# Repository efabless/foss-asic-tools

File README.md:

# IIC-OSIC-TOOLS

This environment is based on the [efabless.com FOSS-ASIC-TOOLS](https://github.com/efabless/foss-asic-tools).

**IIC-OSIC-TOOLS** is an all-in-one Docker container for open-source-based integrated circuit designs for analog and digital circuit flows. The CPU architectures `x86_64/amd64` and `aarch64/arm64` are natively supported based on Ubuntu 22.04LTS (since release `2022.12`). This collection of tools is curated by the [**Institute for Integrated Circuits (IIC), Johannes Kepler University (JKU)**](https://iic.jku.at).

It supports two *modes of operation*:

1. Using a complete desktop environment (XFCE) in `Xvnc` (a VNC server), either directly accessing it with a VNC client of your choice or the integrated [noVNC](https://novnc.com) server that runs in your browser.
2. Using a local X11 server and directly showing the application windows on your desktop.

## How to Use These Open-Source (and Free) IC Design Tools

### Step 1: Clone/download this GitHub repository onto your computer

Use the green **Code** button, and either download the zip file or do a `git clone --depth=1 https://github.com/iic-jku/iic-osic-tools.git`.

### Step 2: Install Docker on your computer

See instructions on how to do this in the section [**Quick Launch for Designers**](#quick-launch-for-designers) further down in this `README`.

### Step 3: Start and Use a Docker Container based on our IIC-OSIC-TOOLS Image

Enter the directory of this repository on your computer, and use one of the methods described in the section [**Quick Launch for Designers**](#quick-launch-for-designers) to start up and run a Docker container based on our image. The easiest way is probably to use the **VNC** mode.

If you do this the first time, or we have pushed an updated image to DockerHub, this can take a while since the image is pulled (loaded) automatically from DockerHub. Since this image is ca. 4GB, this takes time, depending on your internet speed. Please note that this compressed image will be extracted on your drive, so please provide at least **20GB of free drive space**. If, after a while, the consumed space gets larger, this may be due to unused images piling up. In this case, delete old ones; please consult the internet for instructions on operating Docker.

If you know what you are doing and want full root access without a graphical interface, please use `./start_shell.sh`.

## Installed PDKs

As of the `2022.12` tag, the following open-source process-development kits (PDKs) are pre-installed, and the table shows how to switch by setting environment variables (you can do this per project by putting this into `.designinit` as explained below):

| SkyWater Technologies `sky130A` |
|---|
| `export PDK=sky130A` |
| `export PDKPATH=$PDK_ROOT/$PDK` |
| `export STD_CELL_LIBRARY=sky130_fd_sc_hd` |

| Global Foundries `gf180mcuC` |
|---|
| `export PDK=gf180mcuC` |
| `export PDKPATH=$PDK_ROOT/$PDK` |
| `export STD_CELL_LIBRARY=gf180mcu_fd_sc_mcu7t5v0` |

| IHP Microelectronics `sg13g2` |
|---|
| Not yet ready to use |

More options for selecting digital standard cell libraries are available; please check the PDK directories.

## Installed Tools

Below is a list of the current tools already installed and ready to use (note there are some adaptions in our container vs. efabless.com):

* [align](https://github.com/ALIGN-analoglayout/ALIGN-public) automatic layout generation for analog circuits (only on `amd64` and for `sky130` PDK)
* [amaranth](https://github.com/amaranth-lang/amaranth) a Python-based HDL toolchain
* [cace](https://github.com/efabless/cace) a Python-based circuit automatic characterization engine
* [cocotb](https://github.com/cocotb/cocotb) simulation library for writing VHDL and Verilog test benches in Python
* [covered](https://github.com/hpretl/verilog-covered) Verilog code coverage
* [cvc](https://github.com/d-m-bailey/cvc) circuit validity checker (ERC)
* [edalize](https://github.com/olofk/edalize) Python abstraction library for EDA tools
* [fault](https://github.com/Cloud-V/Fault) design-for-test (DFT) solution
* [fusesoc](https://github.com/olofk/fusesoc) package manager and build tools for SoC
* [gaw3-xschem](https://github.com/StefanSchippers/xschem-gaw.git) waveform plot tool for `xschem`
* [gdsfactory](https://github.com/gdsfactory/gdsfactory) Python library for GDS generation
* [gdspy](https://github.com/heitzmann/gdspy) Python module for the creation and manipulation of GDS files
* [gds3d](https://github.com/trilomix/GDS3D) a 3D viewer for GDS files
* [gf180mcu](https://github.com/google/gf180mcu-pdk) GlobalFoundries 180nm CMOS PDK
* [ghdl](https://github.com/ghdl/ghdl) VHDL simulator
* [gtkwave](https://github.com/gtkwave/gtkwave) waveform plot tool for digital simulation
* [sg13g2](https://github.com/IHP-GmbH/IHP-Open-PDK) IHP Microelectronics 130nm SiGe:C BiCMOS PDK (partial PDK, not fully supported yet; `xschem` and `ngspice` simulation works incl. PSP MOSFET model)
* [irsim](https://github.com/rtimothyedwards/irsim) switch-level digital simulator
* [iverilog](https://github.com/steveicarus/iverilog.git) Verilog simulator
* [hdl21](https://github.com/dan-fritchman/Hdl21) analog hardware description library
* [klayout](https://github.com/KLayout/klayout) layout viewer and editor for GDS and OASIS
* [libman](https://github.com/IHP-GmbH/LibMan) design library manager to manage cells and views
* [magic](https://github.com/rtimothyedwards/magic) layout editor with DRC and PEX
* [netlistsvg](https://github.com/nturley/netlistsvg) draws an SVG netlist from a `yosys` JSON netlist
* [netgen](https://github.com/rtimothyedwards/netgen) netlist comparison (LVS)
* [ngspice](http://ngspice.sourceforge.net) SPICE analog and mixed-signal simulator, with OSDI support
* [ngspyce](https://github.com/ignamv/ngspyce) Python bindings for `ngspice`
* [nvc](https://github.com/nickg/nvc) VHDL simulator and compiler
* [open_pdks](https://github.com/RTimothyEdwards/open_pdks) PDK setup scripts
* [openlane](https://github.com/The-OpenROAD-Project/OpenLane) digital RTL2GDS flow
* [openlane2](https://github.com/efabless/openlane2) rewrite of OpenLane in Python, 2nd generation
* [openram](https://github.com/VLSIDA/OpenRAM) OpenRAM Python library
* [openroad](https://github.com/The-OpenROAD-Project/OpenROAD.git) RTL2GDS engine used by `openlane` and `openlane2`
* [osic-multitool](https://github.com/iic-jku/osic-multitool.git) collection of useful scripts and documentation
* [padring](https://github.com/donn/padring) padring generation tool
* [pyopus](https://fides.fe.uni-lj.si/pyopus/index.html) simulation runner and optimization tool for analog circuits
* [pyrtl](https://github.com/UCSBarchlab/PyRTL) collection of classes for pythonic RTL design
* [pyspice](https://github.com/PySpice-org/PySpice) interface `ngspice` and `xyce` from Python
* [pyverilog](https://github.com/PyHDI/Pyverilog) Python toolkit for Verilog
* RF toolkit with [FastHenry2](https://github.com/ediloren/FastHenry2), [FasterCap](https://github.com/ediloren/FasterCap), [openEMS](https://github.com/thliebig/openEMS), and [scikit-rf](https://github.com/scikit-rf/scikit-rf).
* [qucs-s](https://github.com/ra3xdh/qucs_s) simulation environment with RF emphasis
* [rggen](https://github.com/rggen/rggen) code generation tool for configuration and status registers
* [schemdraw](https://github.com/cdelker/schemdraw) Python package for drawing electrical schematics
* [spyci](https://github.com/gmagno/spyci) analyze/plot `ngspice`/`xyce` output data with Python
* [slang](https://github.com/MikePopoloski/slang) SystemVerilog parsing and translation (e.g. to Verilog)
* [synlig](https://github.com/chipsalliance/synlig) SystemVerilog plugin for `yosys`
* [vlog2verilog](https://github.com/RTimothyEdwards/qflow.git) Verilog file conversion
* [volare](https://github.com/efabless/volare) version manager (and builder) for open-source PDKs
* [siliconcompiler](https://github.com/siliconcompiler/siliconcompiler) modular build system for hardware
* [sky130](https://github.com/google/skywater-pdk.git) SkyWater Technologies 130nm CMOS PDK
* [verilator](https://github.com/verilator/verilator) fast Verilog simulator
* [vlsirtools](https://github.com/Vlsir/Vlsir) interchange formats for chip design.
* [xschem](https://github.com/StefanSchippers/xschem.git) schematic editor
* [xyce](https://github.com/Xyce/Xyce.git) fast parallel SPICE simulator (incl. `xdm` netlist conversion tool)
* [yosys](https://github.com/YosysHQ/yosys) Verilog synthesis tool (with GHDL plugin for VHDL synthesis), incl. `eqy` (equivalence checker), `sby` (formal verification), and `mcy` (mutation coverage)

The tool versions used for `OpenLane` are documented in `tool_metadata.yml` and the other tools in `tool_metadata_add.yml`. In addition to the EDA tools above, further valuable tools (like `git`) and editors (like `gvim`) are installed. If something useful is missing, please let us know!

## Quick Launch for Designers

Download and install **Docker** for your operating system:

* [All platforms (Linux)](https://docs.docker.com/engine/install/)
* [Windows](https://desktop.docker.com/win/main/amd64/Docker%20Desktop%20Installer.exe)
* [Mac with Intel Chip](https://desktop.docker.com/mac/main/amd64/Docker.dmg)
* [Mac with Apple Chip](https://desktop.docker.com/mac/main/arm64/Docker.dmg)

Note for Linux: Do not run docker commands or the start scripts as root (`sudo`)! Follow the instructions in [Post-installation steps for Linux](https://docs.docker.com/engine/install/linux-postinstall/)

The following start scripts are intended as helper scripts for local or small-scale (single instance) deployment. Consider starting the containers with a custom start script if you need to run many instances.

### Customizing Environment

All user data is persistently placed in the directory pointed to by the environment variable `DESIGNS` (the default is `$HOME/eda/designs` for Linux/macOS and `%USERPROFILE%\eda\designs` for Windows, respectively).

If a file `.designinit` is put in this directory, it is sourced last when starting the Docker environment. In this way, users can adapt settings to their needs.

### Using VNC and noVNC

This mode is recommended for remote operation on a separate server or if you prefer the convenience of a full desktop environment. To start it up, you can use (in a Bash/Unix shell):

```bash
./start_vnc.sh
```

On Windows, you can use the equivalent batch script (if the defaults are acceptable, it can also be started by double-clicking in Explorer):

```terminal
.\start_vnc.bat
```

You can now access the Desktop Environment through your browser ([http://localhost](http://localhost)). The default password is `abc123`.

#### Variables for VNC

Both scripts will use default settings, which you can tweak by settings shell variables (`VARIABLE=default` is shown):

* `DRY_RUN` (unset by default); if set to any value (also `0`, `false`, etc.), the start scripts print all executed commands instead of running. Useful for debugging/testing or just creating "template commands" for unique setups.
* `DESIGNS=$HOME/eda/designs` (`DESIGNS=%USERPROFILE%\eda\designs` for `.bat`) sets the directory that holds your design files. This directory is mounted into the container on `/foss/designs`.
* `WEBSERVER_PORT=80` sets the port on which the Docker daemon will map the webserver port of the container to be reachable from localhost and the outside world. `0` disables the mapping.
* `VNC_PORT=5901` sets the port on which the Docker daemon will map the VNC server port of the container to be reachable from localhost and the outside world. This is only required to access the UI with a different VNC client. `0` disabled the mapping.
* `DOCKER_USER="hpretl"` username for the Docker Hub repository from which the images are pulled. Usually, no change is required.
* `DOCKER_IMAGE="iic-osic-tools"` Docker Hub image name to pull. Usually, no change is required.
* `DOCKER_TAG="latest"` Docker Hub image tag. By default, it pulls the latest version; this might be handy to change if you want to match a specific version set.
* `CONTAINER_USER=$(id -u)` (the current user's ID, `CONTAINER_USER=1000` for `.bat`) The user ID (and also group ID) is especially important on Linux and macOS because those are the IDs used to write files in the `DESIGNS` directory. For debugging/testing, the user and group ID can be set to `0` to gain root access inside the container.
* `CONTAINER_GROUP=$(id -g)` (the current user's group ID, `CONTAINER_GROUP=1000` for `.bat`)
* `CONTAINER_NAME="iic-osic-tools_xvnc_uid_"$(id -u)` (attaches the executing user's id to the name on Unix, or only `CONTAINER_NAME="iic-osic-tools_xvnc` for `.bat`) is the name that is assigned to the container for easy identification. It is used to identify if a container exists and is running.

To overwrite the default settings, see [Overwriting Shell Variables](#overwriting-shell-variables)

### Using a Local X-Server

This mode is recommended if the container is run on the local machine. It is significantly faster than VNC (as it renders the graphics locally), is more lightweight (no complete desktop environment is running), and integrates with the desktop (copy-paste, etc.). To start the container, run the following:

```bash
./start_x.sh
```

or

```terminal
.\start_x.bat
```

**Attention Windows and macOS users:** The X-server connection is automatically killed if there is a too-long idle period in the terminal (when this happens, it looks like a **crash** of the system). A **workaround** is to start a second terminal from the initial terminal that pops up when executing the start scripts `./start_x.sh` or `.\start_x.bat` and then start `htop` in the initial terminal. In this way, there is an ongoing display activity in the initial terminal, and as a positive side-effect, the usage of the machine can be monitored. We are looking for a better long-term solution.

**Attention macOS users:** Please disable the *Enable VirtioFS accelerated directory sharing* setting available as "Beta Setting," as this will cause issues accessing the mounted drives! However, enabling the *VirtioFS* general setting works in Docker >v4.15.0!

#### Variables for X11

The following environment variables are used for configuration:

* `DRY_RUN` (unset by default), if set to any value (also `0`, `false`, etc.), makes the start scripts print all executed commands instead of running. Useful for debugging/testing or just creating "template commands" for unique setups.
* `DESIGNS=$HOME/eda/designs` (`DESIGNS=%USERPROFILE%\eda\designs` for `.bat`) sets the directory that holds your design files. This directory is mounted into the container on `/foss/designs`.
* `DOCKER_USER="hpretl"` username for the Docker Hub repository from which the images are pulled. Usually, no change is required.
* `DOCKER_IMAGE="iic-osic-tools"` Docker Hub image name to pull. Usually, no change is required.
* `DOCKER_TAG="latest"` Docker Hub image tag. By default, it pulls the latest version; this might be handy to change if you want to match a specific Version set.
* `CONTAINER_USER=$(id -u)` (the current user's ID, `CONTAINER_USER=1000` for `.bat`) The user ID (and also group ID) is especially important on Linux and macOS because those are the IDs used to write files in the `DESIGNS` directory.
* `CONTAINER_GROUP=$(id -g)` (the current user's group ID, `CONTAINER_GROUP=1000` for `.bat`)
* `CONTAINER_NAME="iic-osic-tools_xserver_uid_"$(id -u)` (attaches the executing user's id to the name on Unix, or only `CONTAINER_NAME="iic-osic-tools_xserver` for `.bat`) is the name that is assigned to the container for easy identification. It is used to identify if a container exists and is running.

#### macOS and Windows-specific Variables

For Mac and Windows, the X11 server is accessed through TCP (`:0`, aka port 6000). To control the server's address, you can set the following variable:

* `DISP=host.docker.internal:0` is the environment variable that is copied into the `DISPLAY` variable of the container. `host.docker.internal` resolves to the host's IP address inside the docker containers, `:0` corresponds to display 0 which corresponds to TCP port 6000.

If the executable `xauth` is in `PATH`, the startup script automatically disables access control for localhost, so the X11 server is open for connections from the container. A warning will be shown if not, and you must disable access control.

#### Linux-specific Variables

For Linux, the local X11 server is accessed through a Unix socket. There are multiple variables to control:

* `XSOCK=/tmp/.X11-unix` is typically the default location for the Unix sockets. The script will probe if it exists and, if yes, mount it into the container.
* `DISP` has the same function as macOS and Windows. It is copied to the container's `DISPLAY` variable. If it is not set, the value of `DISPLAY` from the host is copied.
* `XAUTH` defines the file that holds the cookies for authentication through the socket. If it is unset, the host's `XAUTHORITY` contents are used. If those are unset too, it will use `$HOME/.Xauthority`.

The defaults for these variables are tested on native X11 servers, X2Go sessions, and Wayland. The script copies and modifies the cookie from the`.Xauthority` file into a separate, temporary file. This file is then mounted into the container.

#### Installing X11-Server

Everything should be ready on Linux with a desktop environment / UI (this setup has been tested on X11 and XWayland). For Windows and macOS, the installation of an X11 server is typically required. Due to the common protocol, every X11-server should work, although the following are tested:

* For Windows: [VcXsrc](https://sourceforge.net/projects/vcxsrv/)
* For macOS: [XQuartz](https://www.xquartz.org/) **Important:** Please enable *"Allow connections from network clients"* in the XQuartz preferences [CMD+","], tab *"Security"*

For both X-Servers, it is strongly recommended to enable OpenGL:

* The `start_x.sh` script will take care of that on macOS and set it according to configuration values. Only a manual restart of XQuartz is required after the script is run once (observe the output!).
* On Windows with VcXsrv, we recommend using the utility "XLaunch" (installed with VcXsrv):

  * Multiple windows mode
  * Set the Display Number to 0
  * Start no client
  * Tick all `Extra settings`: `Clipboard`, `Primary selection`, `Native opengl`, and `Disable access control`

### Overwriting Shell Variables

#### For the Linux/macOS Bash Scripts

There are multiple ways to configure the start scripts using Bash. Two of them are shown here. First, the variables can be set directly for each run of the script; they are not saved in the active session:

`DESIGNS=/my/design/directory DOCKER_USERNAME=another_user ./start_x.sh`

The second variant is to set the variables in the current shell session (not persistent between shell restarts or shared between sessions):

```bash
export DESIGNS=/my/design/directory
export DOCKER_USERNAME=another_user
./start_x.sh
```

As those variables are stored in your current shell session, you only have to set them once. After setting, you can directly run the scripts.

#### For the Windows Batch Scripts

In `CMD` you can't set the variables directly when running the script. So for the `.bat` scripts, it is like the second variant for Bash scripts:

```batch
SET DESIGNS=\my\design\directory
SET DOCKER_USERNAME=another_user
.\start_x.bat
```

## Support with Issues/Problems/Bugs

We are open to your questions about this container and are very thankful for your input! If you run into a problem and you are sure it is a bug, please let us know by following this routine:

* Take a look at the [KNOWN_ISSUES](KNOWN_ISSUES.md) and the [RELEASE_NOTES](RELEASE_NOTES.md). Both these files can include problems that we are already aware of and maybe include a workaround.
* Check the existing [Issues](https://github.com/iic-jku/IIC-OSIC-TOOLS/issues) on GitHub and see if the problem has been reported already. If yes, please participate in the discussion and help by further collecting information.
* Is the problem in connection with the container, or rather a problem with a specific tool? If it is the second, please also check out the sources of the tool and further contact the maintainer!
* To help us fix the problem, please open an issue on Github and report the error. Please give us as much information as possible without being unneedingly verbose, so filter accordingly. It is also fine to open an issue with very little information, we will help you to narrow down the source of the error.
* Finally, if you can exactly know how to fix the reported error, we are also happy if you open a pull request with a fix!

 Thank you for your cooperation!

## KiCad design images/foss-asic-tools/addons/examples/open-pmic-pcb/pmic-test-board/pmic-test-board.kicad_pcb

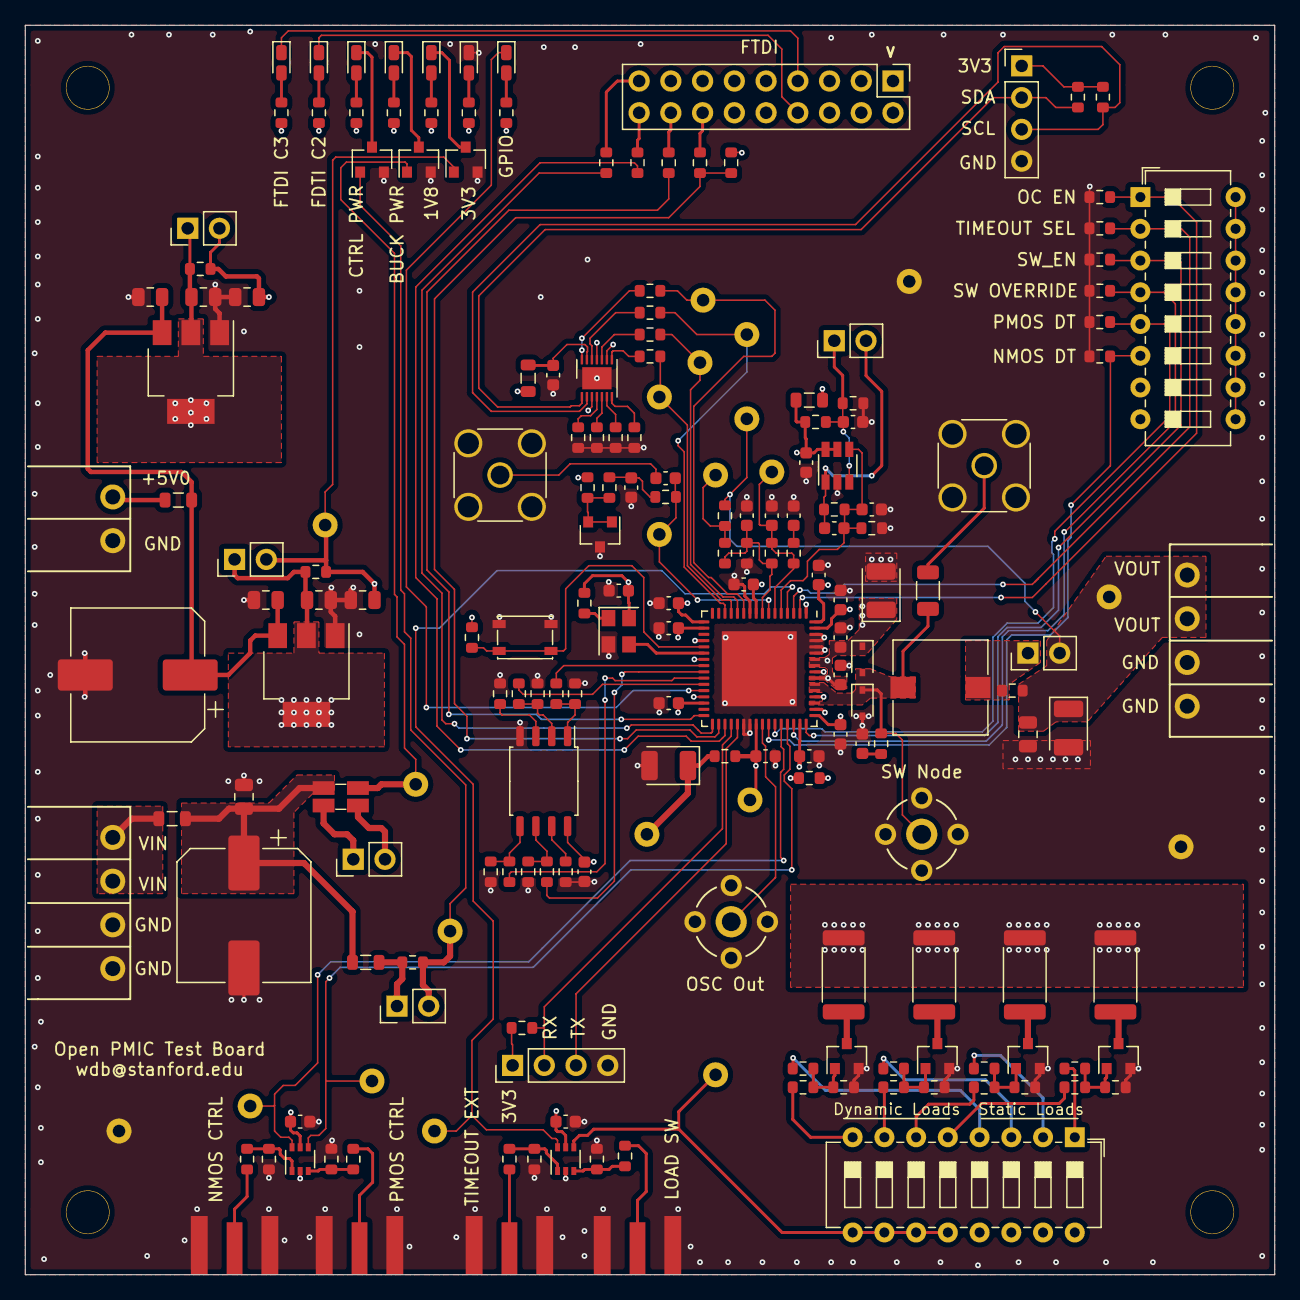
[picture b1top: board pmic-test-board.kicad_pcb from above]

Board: 4 copper layers, 100.0 x 100.0 mm, 205 parts (0 on the bottom side), 120 nets.

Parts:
C101, C106, C401: DNP; C_0603_1608Metric
C102, C206, C211: 47u; CP_EIA-3528-12_Kemet-T
C103, C203, C204, C205, C207, C208, C209, C210: 10u; C_0805_2012Metric
C104: 5.1n; C_0603_1608Metric
C105: 220p; C_0603_1608Metric
C107, C108, C109, C110, C111, C112, C113, C114, C115, C116, C117, C118, C119, C302, C404: 4.7u; C_0603_1608Metric
C120, C121: 0.47u; C_0603_1608Metric
C201, C202: 470u; CP_Elec_10x14.3
C301, C303, C403: C; C_0603_1608Metric
C402: 0.1u; C_0603_1608Metric
D101, D102, D104, D105, D106, D109, D110: LED; LED_0603_1608Metric_Castellated
D107, D108: B0520WS-7-F; D_SOD-323
FB201, FB202, FB203, FB301, FB401: Ferrite_Bead_Small; L_0805_2012Metric
J101, J102, J103, J104: Conn_Coaxial; CONN_SMA_EDGE_SAMTEC_SMA_J_P_H_ST_EM1
J105, J202, J203, J204, J205, J401: Conn_01x02_Male; PinHeader_1x02_P2.54mm_Vertical
J106, J107: Conn_01x04_Male; PinHeader_1x04_P2.54mm_Vertical
J108: Conn_02x09_Odd_Even; PinHeader_2x09_P2.54mm_Vertical
J109, J114: Conn_Coaxial; PK007-015
J110, J301: Conn_Coaxial; SMA_Amphenol_132134_Vertical
J113, J208: Conn_01x04_Female; Terminal-block-plug_4x1_3.5mm-pitch
J115, J116, J117, J118: mounting-hole-nc; M3-mounting-hole-insulated
J207: Conn_01x02_Female; Terminal-block-plug_2x1_3.5mm-pitch
L101: 22u; L_Wuerth_WE-PD-Typ-7345
Q102, Q103, Q104, Q501, Q502, Q503, Q504: BSR202N; SOT-23
R101, R106, R108, R109, R111, R126, R128, R401, R402, R501, R502, R505, R506, R509, R510, R513, R514: 1k; R_0603_1608Metric
R102, R103, R104, R105, R110, R112, R113, R114, R115, R116, R117, R118, R503, R507, R511, R515: 10k; R_0603_1608Metric
R107, R119, R403: DNP; R_0603_1608Metric
R120: 17.6k; R_0603_1608Metric
R121: 40k; R_0603_1608Metric
R122: 7.8k; R_0603_1608Metric
R123, R124, R137, R138: 100; R_0603_1608Metric
R125, R127, R129, R130, R135, R136, R147, R148, R312, R313: 4.7k; R_0603_1608Metric
R131, R132, R133, R134, R143, R144, R145, R146: 47; R_0603_1608Metric
R139: R; R_1206_3216Metric
R140, R141, R142, R304, R306, R307, R308, R309: 0; R_0603_1608Metric
R149: 20; R_0603_1608Metric
R201: 10m; R_Shunt_Ohmite_LVK12
R202, R203, R204: 0.1; R_0603_1608Metric
R301, R302, R404: R; R_0603_1608Metric
R303, R305, R310, R311: 40.2k; R_0603_1608Metric
R504, R508, R512, R516: 24; R_2512_6332Metric
SW101, SW501: SW_DIP_x08; SW_DIP_SPSTx08_Slide_6.7x21.88mm_W7.62mm_P2.54mm_LowProfile
SW102: SW_Push; SW_SPST_PTS810
TP101, TP102, TP103, TP104, TP105, TP106, TP107, TP108, TP109, TP110, TP111, TP201, TP202, TP203, TP301, TP302, TP303, TP304, TP305, TP306, TP401: TestPoint; THM_COMPACT
U101, U102: 74LVC2G34; SOT-363_SC-70-6
U103: W25Q32JVSS; SOIC-8_5.23x5.23mm_P1.27mm
U104: Caravel-QFN; QFN-64-1EP_9x9mm_P0.5mm_EP6x6mm
U201: AZ1117-3.3; SOT-223-3_TabPin2
U202: AZ1117-1.8; SOT-223-3_TabPin2
U301: AZ431LANTR-G1; SOT-23
U302: DS4424N+; TDFN-14-1EP_3x3mm_P0.4mm_EP1.78x2.35mm
U401: LMH6601; TSOT-23-6
X101: ASE-10.000MHZ-LC-T; Oscillator_SMD_Abracon_ASE-4Pin_3.2x2.5mm

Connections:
+1V8: C112.1, C209.1, J203.2, Q102.1, R140.1, R202.1, TP202.1, U104.18
+3V3: C107.1, C108.1, C109.1, C110.1, C114.1, C120.1, C121.1, C210.1, FB301.2, FB401.2, J106.1, J107.1, J204.2, R101.1, R106.1, R108.1, R109.1, R111.1, R117.1, R118.1, R126.1, R128.1, R147.2, R148.2, R203.1, R301.1, R312.2, R313.2, SW101.9, SW101.10, SW101.11, SW101.12, SW101.13, SW101.14, SW101.15, SW101.16, SW501.13, SW501.14, SW501.15, SW501.16, U101.5, U102.5, U103.8, U104.17, U104.30, U104.64, X101.4
/BUCK_VOUT: C102.1, C103.1, J105.2, J113.1, J113.2, R142.1, R149.1, TP102.1, TP105.1
/CTRL_PRW_INJ: C117.1, C118.1, C119.1, R141.1, TP104.1, U104.9, U104.40, U104.47
/FTDI_C2: D109.1, J108.8
/FTDI_C3: D110.1, J108.7
/FTDI_D0: J108.18, R131.2
/FTDI_D1: J108.17, R133.2
/FTDI_D2: J108.16, R134.2
/FTDI_D4: J108.14, R132.2
/GPIO: D101.1, U104.28
/HOST_CSB: R132.1, R147.1, U104.34
/HOST_SCK: R131.1, U104.35
/HOST_SDI: R133.1, U104.33
/HOST_SDO: R134.1, U104.32
/Load/DYN1: R501.1, SW501.8
/Load/DYN2: R505.1, SW501.7
/Load/DYN3: R509.1, SW501.6
/Load/DYN4: R513.1, SW501.5
/Load/STAT1: R502.1, SW501.4
/Load/STAT2: R506.1, SW501.3
/Load/STAT3: R510.1, SW501.2
/Load/STAT4: R514.1, SW501.1
/Power/VIN_CTRL: C202.1, C204.1, C205.1, FB201.1, U201.3, U202.3
/Power/VIN_PWR: C201.1, C203.1, FB202.1, FB203.2, R201.4
/SER_RX: J106.2, R148.1, U104.36
/SER_TX: J106.3, U104.37
/TIA/TIA_3V3: C404.1, FB401.1, R401.1, U401.5, U401.6
/TIA/TIA_SENSE: C403.1, J401.2, R404.1, U401.1
/TIA/TIA_VREF: C402.1, J401.1, R401.2, R402.1, U401.3
/clk: U104.22, X101.3
/flash_clk: R124.2, U104.25
/flash_io0: R137.1, U104.26
/flash_io1: R138.1, U104.27
/flash_~CS: R123.2, U104.24
/nmos_dt: R116.1, SW101.6, U104.42
/nmos_val: TP107.1, U101.6, U104.44
/oc_en: R110.1, SW101.1, U104.2
/osc_monitor: J114.1, U104.41
/pmos_dt: R115.1, SW101.5, U104.43
/pmos_val: TP109.1, U101.4, U104.45
/sw_en: R113.1, SW101.3, U104.48
/sw_override: R114.1, SW101.4, U104.46
/timeout_ext: TP108.1, U102.6, U104.4
/timeout_sel: R112.1, SW101.2, U104.3
/user_vcore: C111.1, C113.1, R140.2, U104.49, U104.63
/vcomp: C105.1, R107.2, R122.1, TP101.1, U104.6
/vfb: C106.1, R107.1, R120.2, R121.1, U104.8
/vsw: D107.2, D108.1, J109.1, L101.1, R119.1, R139.1, U104.51, U104.53, U104.54
/~RST: R118.2, SW102.1, U104.21
BIAS_OC: R309.1, TP305.1, U104.13
BIAS_OPA: R307.1, TP303.1, U104.14
BIAS_OSC: R306.1, TP302.1, U104.11
BIAS_SLOPE: R308.1, TP304.1, U104.12
BUCK_PWR: C115.1, C116.1, C206.1, D107.1, Q103.1, R201.1, TP201.1, U104.55, U104.57, U104.58
BUCK_VOUT: R504.1, R508.1, R512.1, R516.1
CTRL_PWR: C211.1, J205.2, Q104.1, R141.2, R204.1, TP103.1, TP203.1
GND: C101.2, C102.2, C103.2, C104.2, C105.2, C106.2, C107.2, C108.2, C109.2, C110.2, C111.2, C112.2, C113.2, C114.2, C115.2, C116.2, C117.2, C118.2, C119.2, C120.2, C121.2, C201.2, C202.2, C203.2, C204.2, C205.2, C206.2, C207.2, C208.2, C209.2, C210.2, C211.2, C302.2, C303.2, C401.2, C402.2, C404.2, D102.1, D108.2, J101.2, J102.2, J103.2, J104.2, J106.4, J107.4, J109.2, J110.2, J113.3, J113.4, J114.2, J207.1, J208.1, J208.2, J301.2, Q102.2, Q103.2, Q104.2, Q501.2, Q502.2, Q503.2, Q504.2, R102.1, R103.2, R104.1, R105.2, R110.2, R112.2, R113.2, R114.2, R115.2, R116.2, R121.2, R125.1, R127.1, R129.1, R130.1, R135.1, R136.1, R303.2, R305.2, R310.2, R311.2, R402.2, R403.2, R503.2, R507.2, R511.2, R515.2, SW102.2, TP111.1, TP306.1, TP401.1, U101.2, U102.2, U103.4, U104.1, U104.10, U104.20, U104.23, U104.29, U104.38, U104.39, U104.50, U104.52, U104.56, U104.59, U104.60, U104.61, U104.62, U104.65, U201.1, U202.1, U301.3, U302.3, U302.9, U302.11, U302.15, U401.2, X101.2
IMON: C401.1, C403.2, R403.1, R404.2, U104.5, U401.4
LOAD_SW: SW501.9, SW501.10, SW501.11, SW501.12, TP110.1, U102.4
unnamed: C101.1, R119.2
unnamed: C104.1, R122.2
unnamed: C207.1, J204.1, R203.2, U201.2
unnamed: C208.1, J203.1, R202.2, U202.2
unnamed: C301.2, J301.1
unnamed: C302.1, FB301.1, U302.13
unnamed: C303.1, R302.1, R304.2
unnamed: D101.2, R101.2
unnamed: D102.2, R106.2
unnamed: D104.1, Q102.3
unnamed: D104.2, R108.2
unnamed: D105.1, Q103.3
unnamed: D105.2, R109.2
unnamed: D106.1, Q104.3
unnamed: D106.2, R111.2
unnamed: D109.2, R126.2
unnamed: D110.2, R128.2
unnamed: FB201.2, J207.2
unnamed: FB202.2, J208.3, J208.4
unnamed: FB203.1, J205.1, R204.2
unnamed: J101.1, R143.2
unnamed: J102.1, R144.2
unnamed: J103.1, R145.2
unnamed: J104.1, R146.2
unnamed: J105.1, L101.2, R142.2
unnamed: J110.1, R139.2
unnamed: J202.1, R201.3
unnamed: J202.2, R201.2
unnamed: Q501.1, R501.2, R502.2, R503.1
unnamed: Q501.3, R504.2
unnamed: Q502.1, R505.2, R506.2, R507.1
unnamed: Q502.3, R508.2
unnamed: Q503.1, R509.2, R510.2, R511.1
unnamed: Q503.3, R512.2
unnamed: Q504.1, R513.2, R514.2, R515.1
unnamed: Q504.3, R516.2
unnamed: R102.2, R143.1, U101.1
unnamed: R103.1, R144.1, U101.3
unnamed: R104.2, R145.1, U102.1
unnamed: R105.1, R146.1, U102.3
unnamed: R117.2, X101.1
unnamed: R120.1, R149.2, TP106.1
unnamed: R123.1, R125.2, U103.1
unnamed: R124.1, R127.2, U103.6
unnamed: R129.2, U103.7
unnamed: R130.2, U103.3
unnamed: R135.2, R138.2, U103.2
unnamed: R136.2, R137.2, U103.5
unnamed: R301.2, R302.2, U301.1, U301.2
unnamed: R303.1, U302.7
unnamed: R305.1, U302.6
unnamed: R306.2, U302.14
unnamed: R307.2, U302.12
unnamed: R308.2, U302.10
unnamed: R309.2, U302.8
unnamed: R310.1, U302.5
unnamed: R311.1, U302.4
SCL: J107.3, R313.1, U302.2
SDA: J107.2, R312.1, U302.1
VREF: C301.1, R304.1, TP301.1, U104.7

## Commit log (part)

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2023-02-01 Remove spice.rc, as .spiceinit is used
2023-02-01 Remove spice.rc
2023-02-02 Harmonize license and status messages in scripts
2023-02-05 Update alias for klayout and magic
2023-02-05 Remove local copies of klayout tech files
2023-02-05 Bump tool versions and include first example
2023-02-08 Removing the -l option in the alias, as klayout is ignoring it when -nn is given
2023-02-08 Bump version
2023-02-08 Repair install of jupyterlab
2023-02-10 Add gf180mcu PDK to install list
2023-02-15 Remove gf180mcuD process flavor
2023-02-28 Initial State
2023-02-28 Align + Align-Sky130 integration
2023-03-06 Adding package for venv
2023-03-07 Fixed typo
2023-03-07 Update Dockerfile
2023-03-07 Updated Dockerfile & design.
2023-03-07 Updated Align install.
2023-03-07 Changed installation of virtualenv.
2023-03-07 Added design example - inverter.
2023-03-07 Adding python packages (tk and pyyaml)
2023-03-08 Add python packages tk and venv for 22.04 as well
2023-03-11 Rename EDA server scripts
2023-03-11 Refactor eda_server scrips
2023-03-11 Vars moved to config file
2023-03-11 Add script for restarting eda server, adapt others
2023-03-12 Improve install of ngspyce
2023-03-12 Include IHP sg13g2 PDK
2023-03-12 Add ngspyce, fix libngspice version
2023-03-13 Add IHP pdk and openram, and fix a few grammar issues on the way
2023-03-13 Added firefox from Mozilla PPA. Prevent installing it with Snap.
2023-03-13 Install required tools before adding PPA.
2023-03-14 Bump versions
2023-03-14 Fixed typo.
2023-03-14 Updated typo.
2023-03-14 Integrated automated port placement.
2023-03-14 Updated the inverter example.
2023-03-14 Included folded cascode amplifier example.
2023-03-14 Created python script to generate ports from labels in magic.
2023-03-14 Changed name of spice_to_sp_2 to spice_to_sp
2023-03-14 Bump version (important for IIC-LVS script)
2023-03-14 Revert fault version
2023-03-15 Improve dependencies and build script of RV tools
2023-03-16 Bump OL to latest version
2023-03-19 Fix magic layout window garbage on macOS using XQuartz
2023-03-21 Update build scripts
2023-03-21 Removed starting of venv and renamed to iic-align.
2023-03-24 Remove tempory WA
2023-03-28 Fine tuning.
2023-03-28 Added alias to start iic-align design script.
2023-03-28 Rechanged to original.
2023-03-28 Revert "Revert "Merge remote-tracking branch 'origin/next_release' into align_integration""
    This reverts commit 0c4e908ee97318933ea7277af16debd17f593a12.
2023-03-28 Reseted to working stage.
2023-03-28 Revert "Revert "Fine tuning.""
    This reverts commit 0e94b5413576d08f449f0061ce1a0f4d98f0e7a6.
2023-04-04 Try to fix Jinja dependencies.
2023-04-10 Split EDA packages from `dependencies` into `install`, remove Ubuntu 20.04 support
2023-04-10 Use split base build, merged libngspice build (see 650bfe8f916564766ff4fcd185ac1d6898c2b6fa and c9b7c8626e1897ddad8c5b3a4b68c77ed0386fa2)
2023-04-11 Bump tool versions
2023-04-11 Move one package, remove libngspice
2023-04-12 Temporay WA for OpenSTA segfault
2023-04-12 Bump xschem
2023-04-18 Remove OpenROAD STA patch
2023-04-19 Improved network security sideffect, use DNS from Google by default, automatic restart
2023-04-20 Verilator now controlled by OpenLane, bump tool versions
2023-04-21 Roll back OL1 version, latest crashes, so leave for next release
2023-04-24 Replace absolute paths by proper env var (and fix some linting issues along the way)
2023-04-25 Reorganize addons into a `skel` so that a single copy is sufficient
2023-04-25 Add script dir to skeleton
2023-04-25 Move files to correct position in skeleton
2023-04-26 Adapted align integration to new format.
2023-05-16 Added start_jupyter for windows
2023-05-16 Disabled echo in start_jupyter for windows
2023-05-20 Improve build of FasterCap
2023-05-20 Fix typo
2023-05-22 Allow custom container names
2023-05-22 Removed unused stuff/parameters from the start_jupyter.bat script.
2023-05-22 Add nicer names for FasterCap
2023-05-22 Fix build on aarch64
2023-05-22 Add openems
2023-05-22 WA for OpenLane, otherwise crash on linting step, see https://github.com/The-OpenROAD-Project/OpenLane/issues/1811
2023-05-23 Addition of Qucs-S (TODO is proper configuration, likely via skel)
2023-05-24 Addition of PyOPUS
2023-05-25 Add some clear instructions on how to get started
2023-05-26 Add hint with NB URL
2023-05-26 Rename IIC-OSIC to OSIC-MULTITOOL
2023-05-29 Rename IIC-OSIC to OSIC-MULTITOOL cont'd
2023-05-29 Remove remaining 20.04 code snippets, upgrade Swift to 5.8
2023-05-29 Bump Boost version
2023-05-31 Install doc and demos, WA for Python package `datatable`
2023-05-31 Modified ui_startup.sh: Now the whole script (and therefore the container) exits when one of the sub-processes (VNC, NoVNC) stops. The log is now merged and sent to the docker daemon through stdout/s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
2023-06-13 Updated port placing mechanism.
2023-06-13 Exchanged spice_to_sp with cir2align
2023-06-19 Use filter on `git clone` to make it faster
2023-06-19 Remove WA, faster `git clone`
2023-06-20 Remove sky130B (to save space)
2023-06-30 Bump OL version
2023-07-07 Bump version, use our repo for ALIGN PDK
2023-07-07 Add ALIGN
2023-07-07 Set x flag
2023-07-07 Update iic-align.sh
    Updated .magicrc path.
    Updated /foss/tools/ to ${TOOLS}
2023-07-07 Update iic-align.sh
    Updated Paths.
2023-07-10 Changed path of ALIGN design script.
    Developed design scripts for ALIGN are now located in align-utils.
2023-07-10 Changed path of ALIGN design script.
2023-07-11 Add slang package
2023-07-17 Fixed wrong path to cir2align.py
2023-07-17 Updated align-pdk-sky130 repo commit.
2023-07-18 Set +x on script
2023-08-02 Fix build fail
2023-08-02 Add new dependency for OR
2023-08-17 Revert gtkwave version due to build fail
2023-08-23 FEAT: First piel integration atempt
2023-09-05 Correct typo
2023-09-17 Prepore for release
2023-09-17 New dependency for `OpenLane`
2023-09-18 Pin volare version due to fail
2023-09-18 Remove temporary WA
2023-09-25 Added a file for automatic citation generation on GitHub.
2023-10-14 Add OpenVAF
2023-10-15 Add comment that LLVM<15 is needed
2023-10-15 Move to LLVM-14/Clang-14
2023-10-18 Bump versions, ngspice build based on open_pdks
2023-10-18 Build PSP model (only on `amd64` for now) and install in ngspice proper location, plus enable the OSDI read
2023-10-19 PSP model only on x86_64 for now
2023-10-21 Remove OpenVAF build for now
2023-10-22 Add comment
2023-10-22 Get rid of GCC-10
2023-10-24 OpenVAF now also works on `aarch64`
2023-10-28 Bump tool versions, rename `QUCS` variables to `QUCS_S`
2023-10-29 Bump version of BOOST and OR-Tools, add flask (for yosys.mcy)
2023-10-29 Rolling back update of BOOST and OR-Tools (build fail on Xyce)
2023-10-30 Finish proper inclusion of eqy/sby/mcy
2023-10-31 Added build for OpenVAF, currently including a Patch to successfully build ucrt.c.
2023-11-01 Get rid of old gcc-9 stuff
2023-11-01 Use locally-built `OpenVAF` in build process
2023-11-01 Rename variable
2023-11-15 Set Python cache dir (e.g. for IHP PyCells)
2023-11-16 Remove `pre_osdi` statements from examples
2023-11-17 Remove `pre_osdi` statements from examples (now functional implementation)
2023-11-20 Update gtkwave rev
2023-11-27 Add FIXME
2023-11-30 README.md: Additional code quotes
2023-11-30 .bashrc: Enable colorized ls
2023-12-02 Required for `klayout`, see https://github.com/iic-jku/IIC-OSIC-TOOLS/pull/20/files#diff-8c12424239599ac95ce2dd187d671d09d7a3ae088c6952f99e469baa01ccb76a
2023-12-02 Dependencies for xschem and OpenROAD
2023-12-08 Required for `cocotb`
2023-12-09 Adding `scikit-rf`
2023-12-28 Adding `schemdraw`
2023-12-28 Fix PATH for `atalanta`
2023-12-28 Fix `atalanta` build
2023-12-28 Adding `klayout` Python package for `OpenLane` and `OL2`
2023-12-29 Revert "Adding `klayout` Python package for `OpenLane` and `OL2`"
    This reverts commit 4b543a5a42db77aba2a69182490da1c6edbe4c8a.
2023-12-29 Bump `KLayout` version to 0.28.13, to be used by OL1 and OL2
2024-01-08 Add alternative location for BOOST build
2024-01-08 .gitignore: Add comment sections
2024-01-08 .gitignore: Ignore editor swap/backup files
2024-01-08 dependencies.sh: Download boost source archive from GitHub instead of jfrog
2024-01-09 Revert version of PyOPUS, something is wrong with 0.11.1
2024-01-09 Adding `virtualenv`
2024-01-09 Remove unused line
2024-01-09 Revert "Remove unused line"
    This reverts commit 5c7206843263006e3bd5c8b3430afedbdb5a3072.
2024-01-09 Adding VS Code
2024-01-09 Add APT source for VS Code, improved Ubuntu version detection
2024-01-09 Support for proxy with auth (affects git, apt-add-repository)
2024-01-09 Remove openEMS, as this pulls a lot of other python3-* packages via APT
2024-01-12 Add gf180mcuD for PICO Chipathon
2024-01-14 Bump tool version, `xschem` and `qflow` with important bugfixes
2024-01-16 Reworked base image build. Split the huge dependencies.sh into multiple scripts/RUN in the Dockerfile. Moved adding user repos to the image finalization (thats where they are actually installed).
2024-01-16 Adding ipympl (see https://github.com/iic-jku/IIC-OSIC-TOOLS/issues/34)
2024-01-17 Handle HTTP/s proxy when receiveing GPG keys
2024-01-18 Fix the split base image scripts. Every script needs to be copied after another, or otherwise, if one file is changed, all scripts are copied and each one is executed again.
2024-01-18 Added additional pip3 packages for BAG2
2024-01-18 BAG2 install script: create a sourceme.sh script tailored for IIC-OSIC
2024-01-18 Reenable IHP build (temporarily deactivated due to build errors)
2024-01-18 Source the BAG2 sourceme.sh script in final .bashrc
2024-01-18 BAG2 Tool Integration: added install script
2024-01-19 Revert "Merge pull request #25 from martinjankoehler/bag2_integration"
    This reverts commit 87ec325f68ff9c0dacbf318e2f1af0c918db9dbf, reversing
    changes made to e2b85ea9edefbab2b3db003e7f69350b5d5bd12f.
    Some tool breaks overserved (e.g. ngspice, klayout) thus reverting.
2024-01-19 Remove unconfined seccomp setting. It is probably not needed (and poses a potential security issue when the container is open to the public).
2024-01-19 Removed unused variables from startscript (seccomp unconfined not needed).
2024-01-23 Bump tool version, prepare for release
2024-01-24 Added known issues markdown file.
2024-01-24 Added instructions on how to report an error. Referenced to the release notes and known issues files. Added openems as fixed in the release notes.
2024-01-30 Pull image on container start for start_jupyter and start_x, don't (automatically) do it for VNC and shell.
2024-02-05 Add a simple digital (counter) and a simple analog (inverter) example
2024-02-05 Add libman
2024-02-06 Add debug message
2024-02-06 Fix GH repo location
2024-02-16 Adding required pkgs for RALF
2024-02-24 Bump Swift version to latest
2024-02-24 Expand version label
2024-02-24 Add reduced `sky130` model files for SF and FS
2024-02-25 Fix typos
2024-02-25 Add known issues of`Fault` and `Align`
2024-02-28 Adding `synlig` SystemVerilog plugin for Yosys
2024-02-28 Adding `KLAYOUT_HOME` for IHP PDK
2024-03-03 Add packages for `synlig`
2024-03-05 Adding `xarchiver`
2024-03-05 Release of `2024.02` skipped
2024-03-10 Get many Python packages from APT (rather then PIP)
2024-03-12 Sort packages
2024-03-12 Moved here from `install.sh`
2024-03-14 Adding `control` Python toolbox
2024-03-14 FIXME: Remove hdl21 due to build fail
2024-03-14 Bumping tool versions
2024-03-20 Remove RISC-V Toolchain from container.
    We do not see much usage, but saves 1.7 GB uncompressed.
2024-03-20 Remove build-directory from align
    Otherwise it ends up in the container, but is unneeded.
2024-03-20 Rename basepkg install script.
